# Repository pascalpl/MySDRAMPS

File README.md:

My variation of http://reprap.org/wiki/Sdramps. Ready for DIY manufacturing.
Single layer PCB.

Parts:
http://sklep.avt.pl/zlacze-kart-sd-z-wyrzutnikiem.html
http://sklep.avt.pl/uklad-scalony-ncp1117dt33g.html

Library for Eagle in lbr/ folder.

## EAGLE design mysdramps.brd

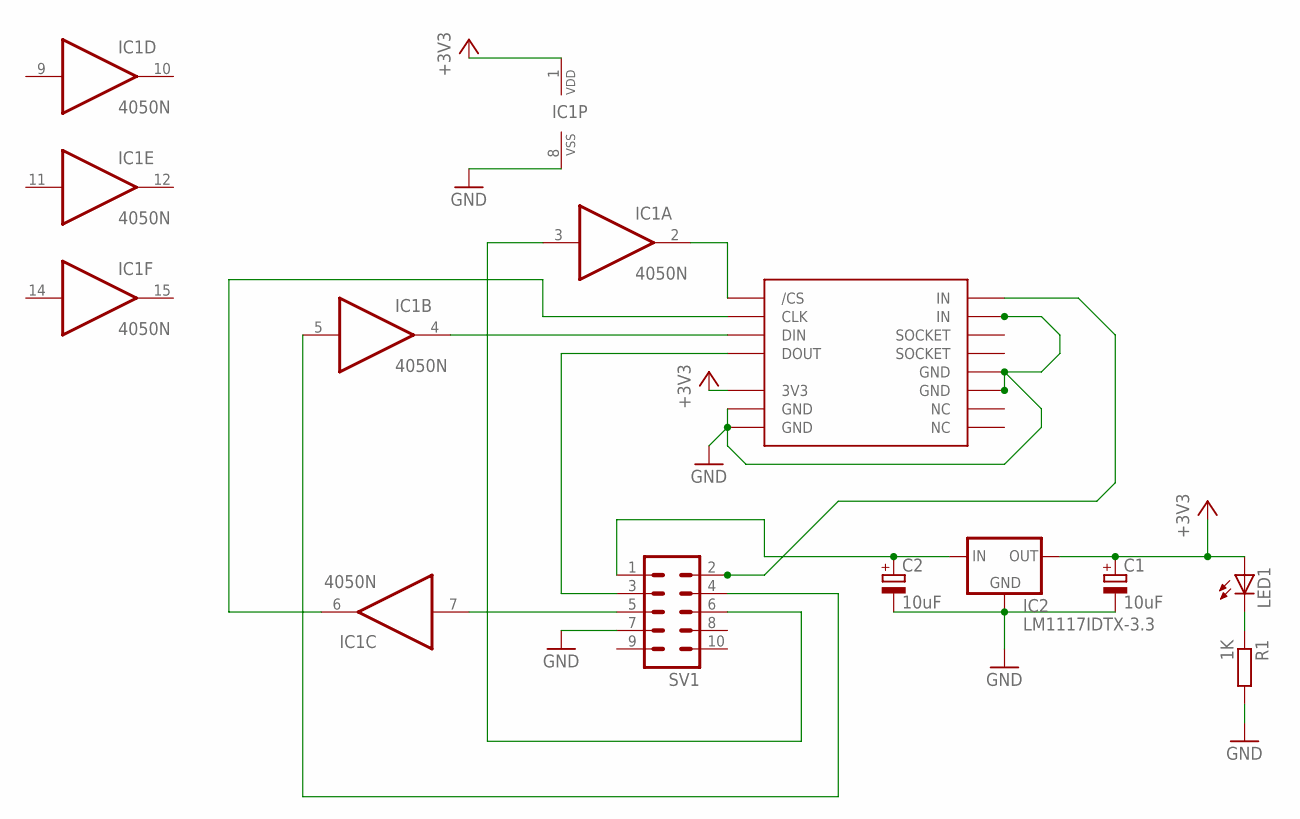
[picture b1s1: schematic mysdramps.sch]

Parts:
C1, C2: 10uF; E5-5
IC1: 4050N; DIL16
IC2: LM1117IDTX-3.3; TO252
LED1: LED_ELD260; LED_LD260
R1: 1K; 0207/7
SV1: MA05-2
U$1: MMC; MMC_SOCKET

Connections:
+3V3: C1.+, IC1.1 (VDD), IC2.TAB (OUT), LED1.A, U$1.3V3
GND: C1.-, C2.-, IC1.8 (VSS), IC2.1 (GND), R1.2, SV1.7, U$1.GND@1 (GND), U$1.GND@2 (GND), U$1.GND@3 (GND), U$1.GND@4 (GND), U$1.IN@2 (IN)
unnamed: SV1.3, U$1.DOUT
unnamed: LED1.K (C), R1.1
unnamed: C2.+, IC2.2 (IN), SV1.1
unnamed: IC1.2 (O), U$1./CS
unnamed: IC1.3 (I), SV1.6
unnamed: IC1.4 (O), U$1.DIN
unnamed: IC1.5 (I), SV1.4
unnamed: IC1.6 (O), U$1.CLK
unnamed: IC1.7 (I), SV1.5
unnamed: SV1.2, U$1.IN@1 (IN)

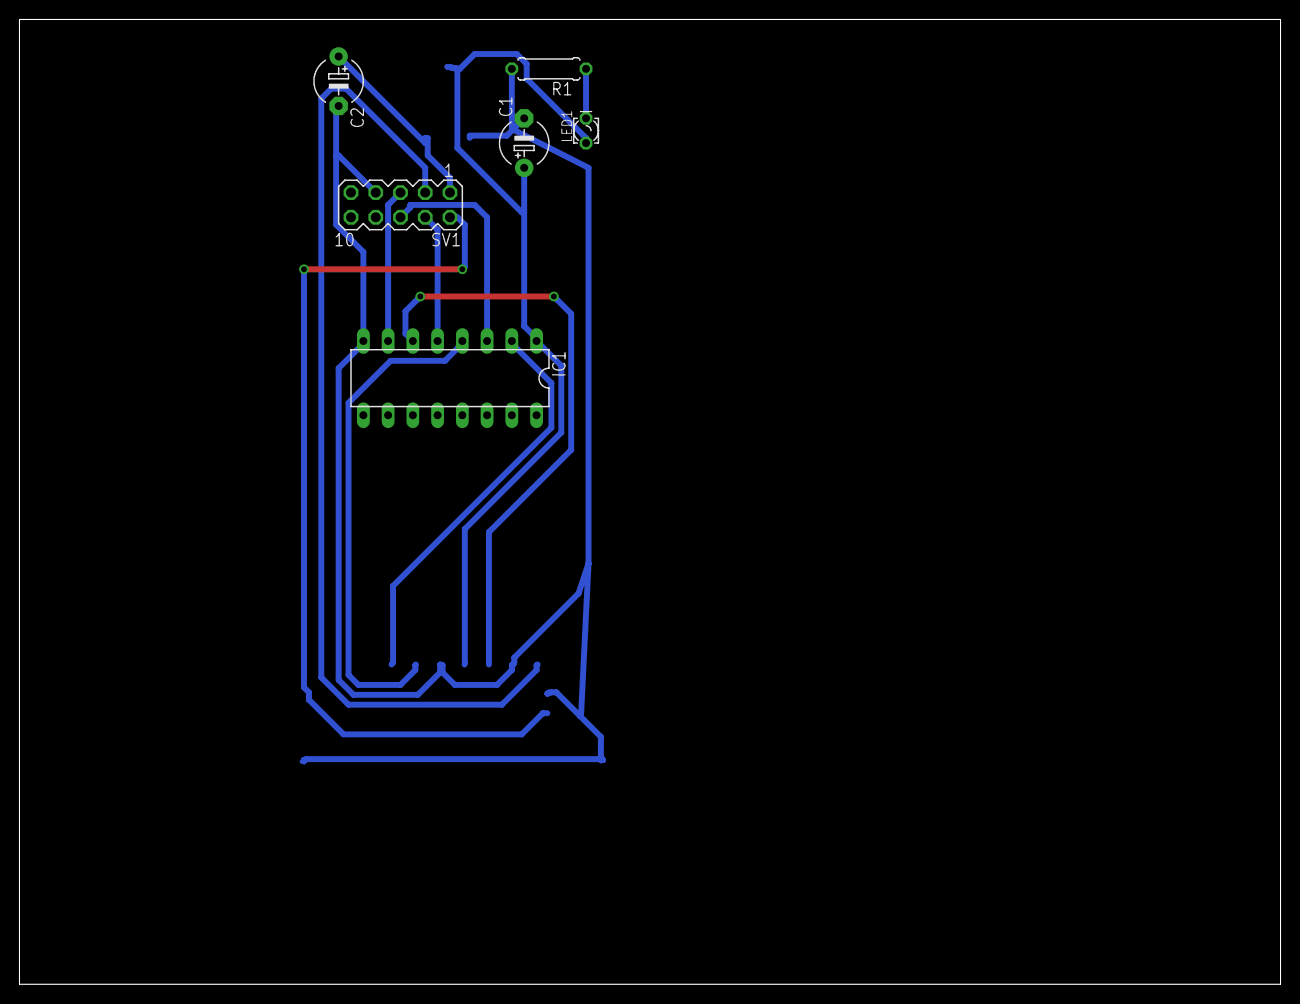
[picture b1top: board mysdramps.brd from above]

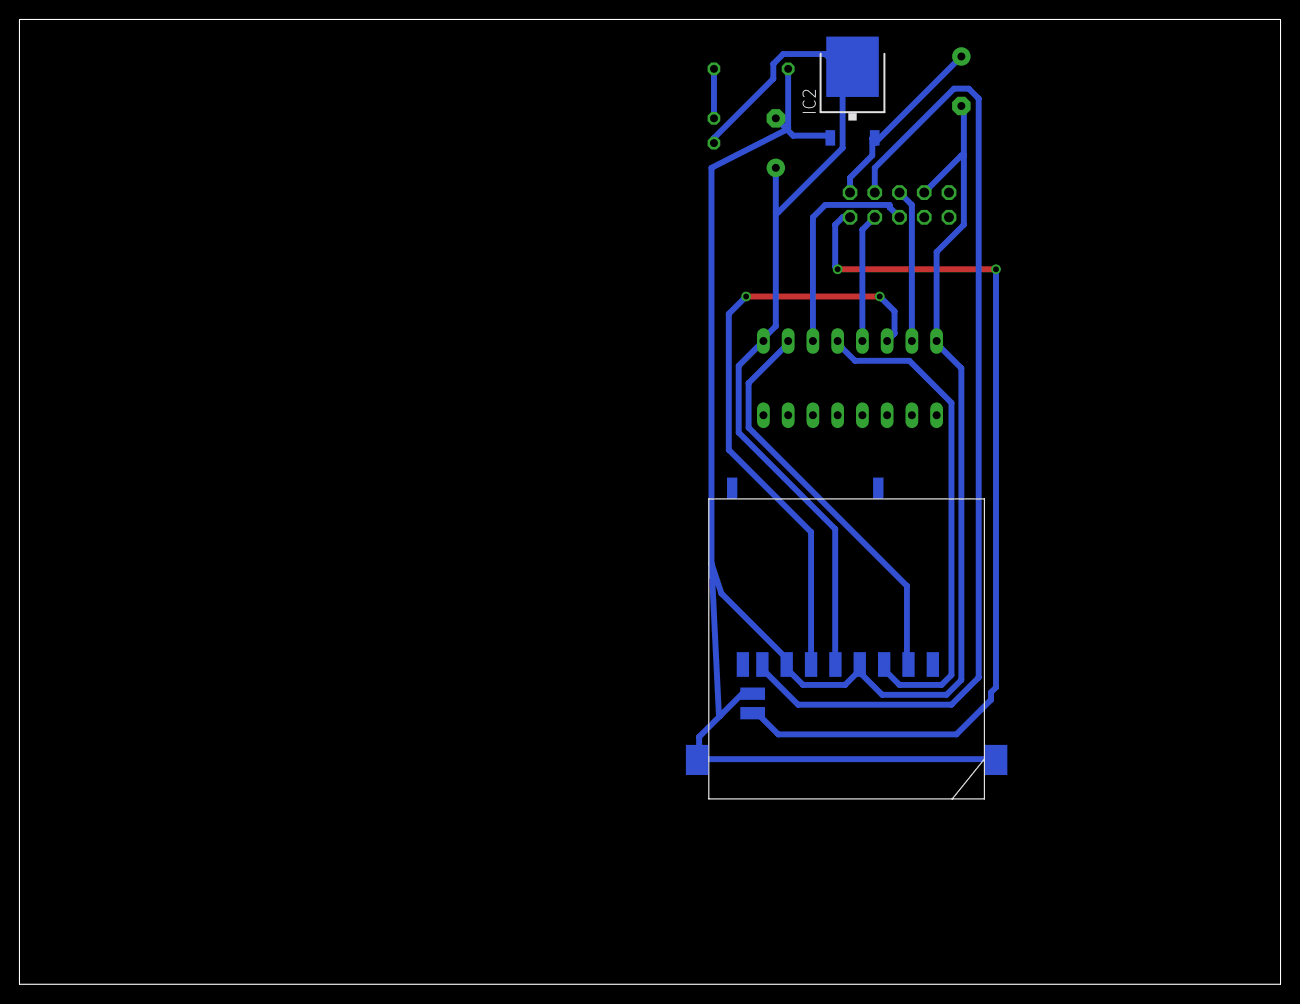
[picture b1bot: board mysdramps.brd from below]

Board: 2 copper layers, 129.5 x 99.0 mm, 8 parts (2 on the bottom side), 12 nets.
